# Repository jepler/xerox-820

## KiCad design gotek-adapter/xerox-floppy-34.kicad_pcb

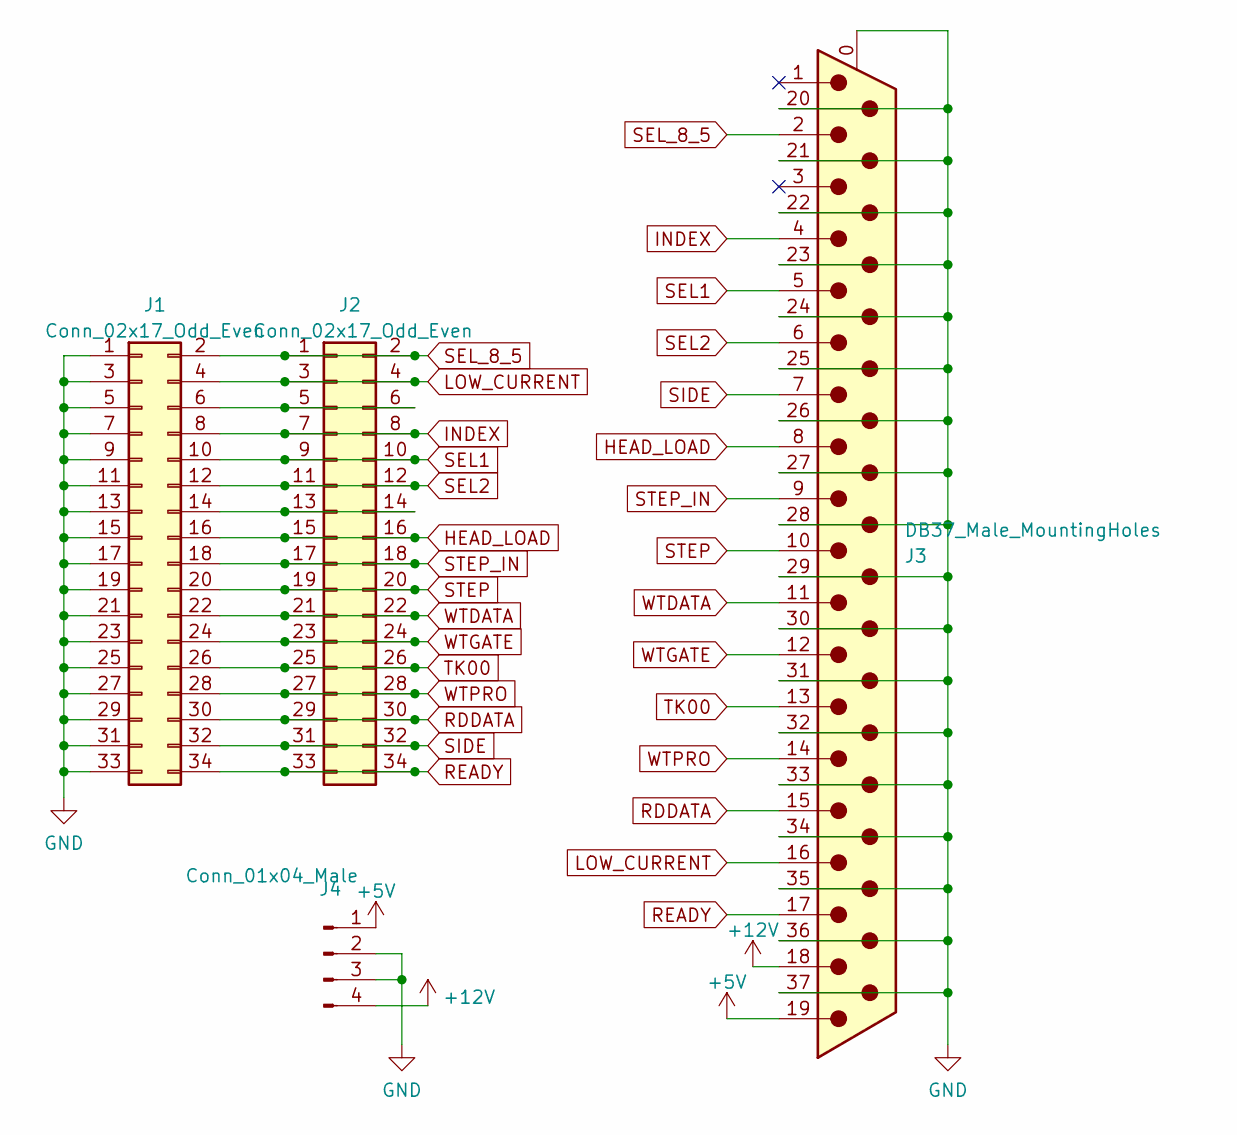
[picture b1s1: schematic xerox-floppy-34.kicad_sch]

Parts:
J1: Conn_02x17_Odd_Even; PinHeader_2x17_P2.54mm_Horizontal
J2: Conn_02x17_Odd_Even; PinHeader_2x17_P2.54mm_Vertical
J3: DB37_Male_MountingHoles; DSUB-37_Male_Horizontal_P2.77x2.84mm_EdgePinOffset9.90mm_Ho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
J4: Conn_01x04_Male; JST_EH_S4B-EH_1x04_P2.50mm_Horizontal

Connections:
+5V: J3.19, J4.1
+12V: J3.18, J4.4
GND: J1.1, J1.3, J1.5, J1.7, J1.9, J1.11, J1.13, J1.15, J1.17, J1.19, J1.21, J1.23, J1.25, J1.27, J1.29, J1.31, J1.33, J3.0 (PAD), J3.20, J3.21, J3.22, J3.23, J3.24, J3.25, J3.26, J3.27, J3.28, J3.29, J3.30, J3.31, J3.32, J3.33, J3.34, J3.35, J3.36, J3.37, J4.2, J4.3
HEAD_LOAD: J1.16, J2.15, J2.16, J3.8
INDEX: J1.8, J2.7, J2.8, J3.4
LOW_CURRENT: J1.4, J2.3, J2.4, J3.16
unnamed: J1.6, J2.5, J2.6
unnamed: J1.14, J2.13, J2.14
RDDATA: J1.30, J2.29, J2.30, J3.15
READY: J1.34, J2.33, J2.34, J3.17
SEL1: J1.10, J2.9, J2.10, J3.5
SEL2: J1.12, J2.11, J2.12, J3.6
SEL_8_5: J1.2, J2.1, J2.2, J3.2
SIDE: J1.32, J2.31, J2.32, J3.7
STEP: J1.20, J2.19, J2.20, J3.10
STEP_IN: J1.18, J2.17, J2.18, J3.9
TK00: J1.26, J2.25, J2.26, J3.13
WTDATA: J1.22, J2.21, J2.22, J3.11
WTGATE: J1.24, J2.23, J2.24, J3.12
WTPRO: J1.28, J2.27, J2.28, J3.14

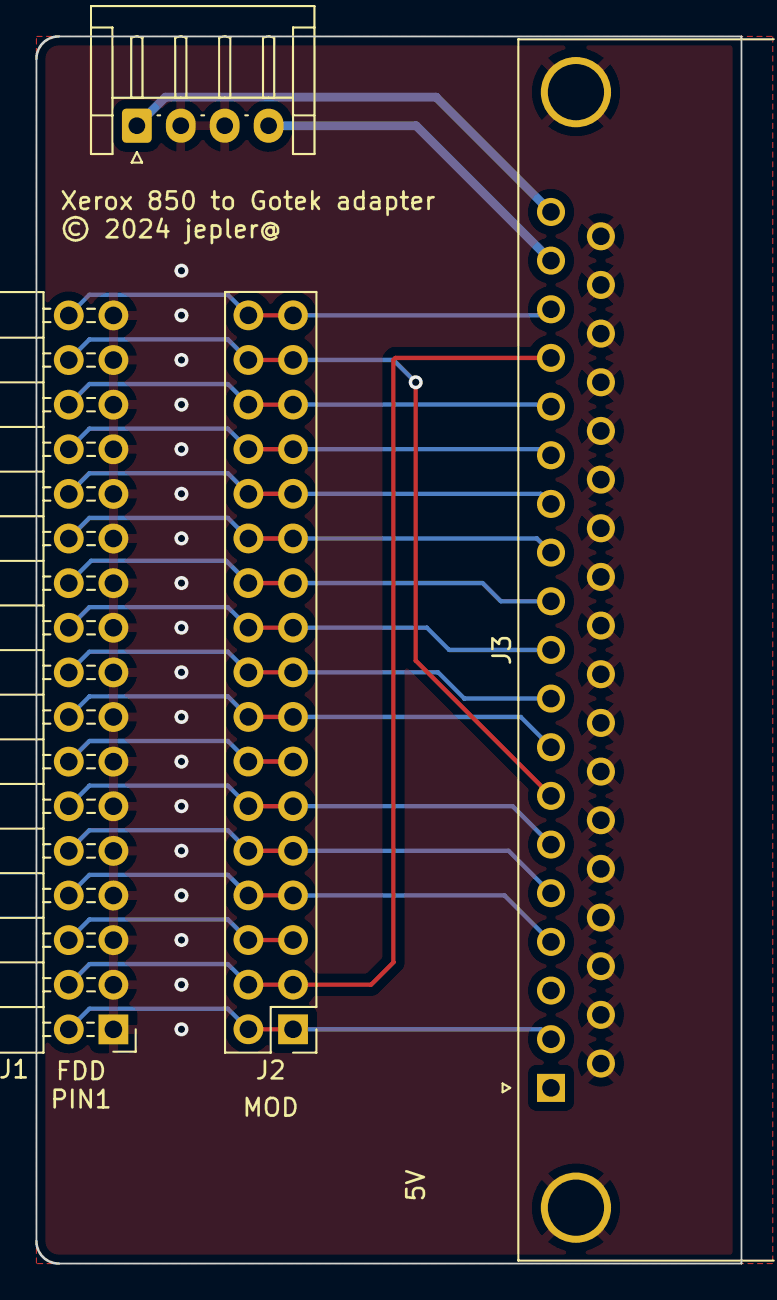
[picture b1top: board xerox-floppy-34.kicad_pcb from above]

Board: 2 copper layers, 40.1 x 69.8 mm, 4 parts (0 on the bottom side), 20 nets.

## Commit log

2023-05-12 collected some docs from the internet
2023-05-12 some pc-side scripts I wrote
2023-05-12 the drives
2023-05-12 moar stuf
2023-05-12 cbios
2023-05-12 another manual
2023-05-12 WIP-xmodem
2023-05-13 add shebangs, make pusher more robust
2023-05-13 finish xmodem port
    typical commandline on sender:
    (stty 19200; sx -vv XMODEM5.com ) < /dev/ttyUSB0 > /dev/ttyUSB0
    on receiver:
    xmodem X.COM /r /c
2023-05-21 Xerox 820 ROM-based monitor version 2.0, Disassembled by K1BC
    .. as imaged from one of my floppies
2023-05-22 various disk images
2023-05-23 this makes the firmware, sorta
2023-05-23 add zmac, ld80
2023-05-23 remove binary files committed by mistake
2023-05-23 handy symlinks
2023-05-23 builds PROM, untested
2023-05-23 the .com live-firmware-patcher works!
2023-05-23 prom: Make SIO B into a sort of console replacement
    I'd move this to A but I'm lazy rn.
    After booting CPM, have to switch to 1200 baud for now.
    Should make it a build option.
2023-05-23 SIO A works, just needs a null modem
2023-05-28 more disk images (is that the last of 'em?)
2023-06-03 Add more targets
    .. these new h/l hex files are for flashing, wooo!
2023-06-03 com 8116 baud rate generator
2024-04-21 some new datasheets
2024-04-24 add gotek adapter kicad files
2024-11-04 flashfloppy config for 8" models

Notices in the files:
gotek-adapter/xerox-floppy-34.kicad_pcb:
© 2024 jepler@
